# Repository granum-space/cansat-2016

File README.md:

# cansat-2016
проект команды granum конкурса cansat 2016

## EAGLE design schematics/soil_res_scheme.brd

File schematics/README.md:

# cansat-2016
Электронные схемы аппарата

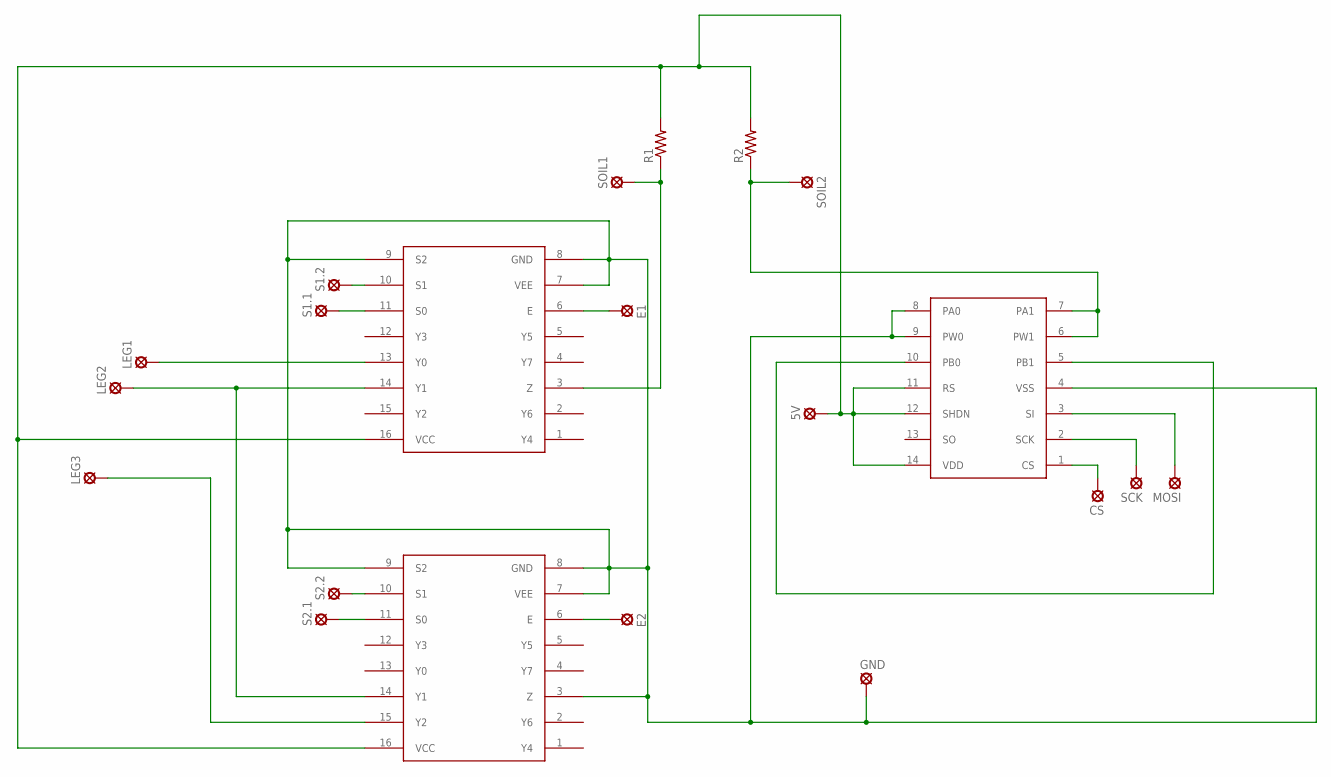
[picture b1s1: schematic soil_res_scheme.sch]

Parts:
5V: LSP10
CS: LSP10
E1, E2: LSP10
GND: LSP10
LEG1, LEG2, LEG3: LSP10
MOSI: LSP10
R1, R2: R-US_0207/10; 0207/10
S1.1, S1.2, S2.1, S2.2: LSP10
SCK: LSP10
SOIL1, SOIL2: LSP10
U$1: MCP42100!; DIL14
U$2, U$3: 74HC4051!; DIL16

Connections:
5V: 5V.MP, R1.2, R2.2, U$1.11 (RS), U$1.12 (SHDN), U$1.14 (VDD), U$2.16 (VCC), U$3.16 (VCC)
CS: CS.MP, U$1.1 (CS)
E1: E1.MP, U$2.6 (E)
E2: E2.MP, U$3.6 (E)
GND: GND.MP, U$1.4 (VSS), U$1.8 (PA0), U$1.9 (PW0), U$2.7 (VEE), U$2.8 (GND), U$2.9 (S2), U$3.3 (Z), U$3.7 (VEE), U$3.8 (GND), U$3.9 (S2)
MOSI: MOSI.MP, U$1.3 (SI)
unnamed: S2.2.MP, U$3.10 (S1)
unnamed: S2.1.MP, U$3.11 (S0)
unnamed: S1.1.MP, U$2.11 (S0)
unnamed: S1.2.MP, U$2.10 (S1)
unnamed: LEG1.MP, U$2.13 (Y0)
unnamed: LEG2.MP, U$2.14 (Y1), U$3.14 (Y1)
unnamed: LEG3.MP, U$3.15 (Y2)
unnamed: U$1.5 (PB1), U$1.10 (PB0)
SCK: SCK.MP, U$1.2 (SCK)
SOIL-1: R1.1, SOIL1.MP, U$2.3 (Z)
SOIL-2: R2.1, SOIL2.MP, U$1.6 (PW1), U$1.7 (PA1)

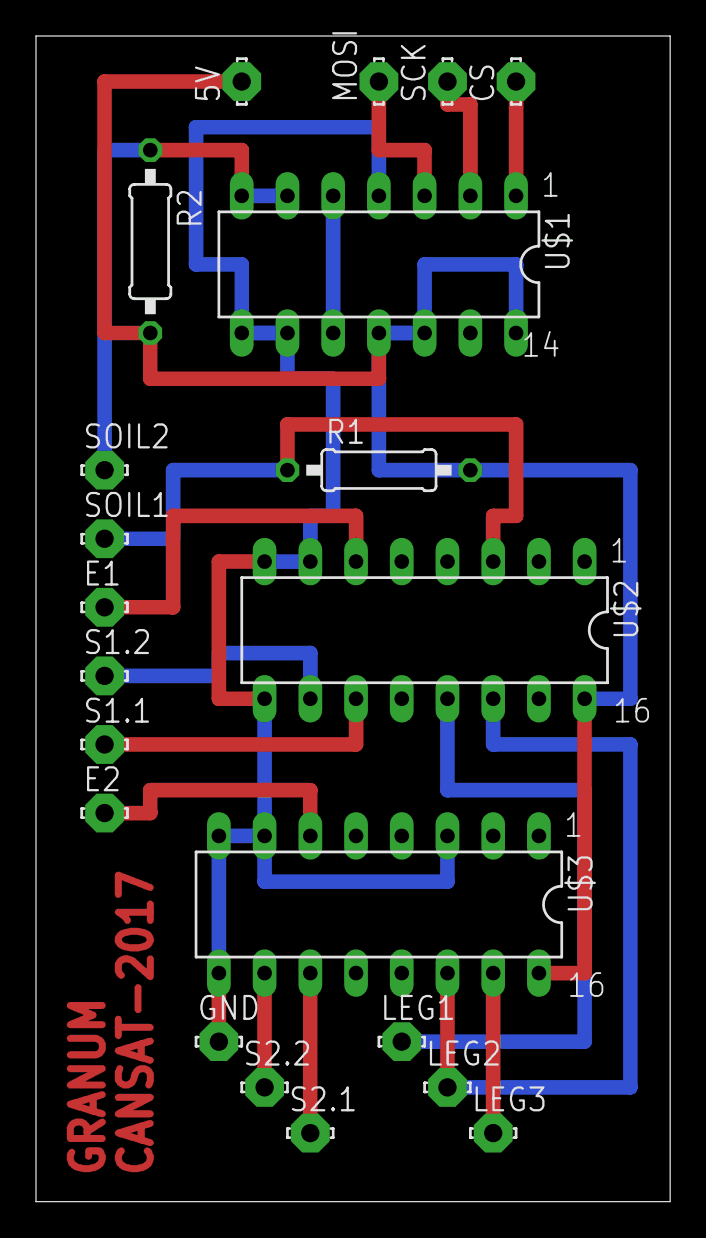
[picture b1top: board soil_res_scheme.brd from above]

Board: 2 copper layers, 35.2 x 64.8 mm, 21 parts (0 on the bottom side), 17 nets.

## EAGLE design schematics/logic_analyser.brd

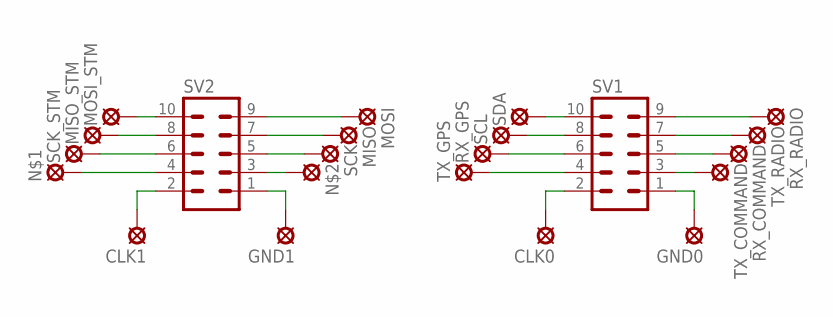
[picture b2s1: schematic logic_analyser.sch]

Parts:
CLK0, CLK1: LSP10
GND0, GND1: LSP10
MISO: LSP10
MISO_STM: LSP10
MOSI: LSP10
MOSI_STM: LSP10
N$1, N$2: LSP10
RX_COMMAND: LSP10
RX_GPS: LSP10
RX_RADIO: LSP10
SCK: LSP10
SCK_STM: LSP10
SCL: LSP10
SDA: LSP10
SV1, SV2: MA05-2
TX_COMMAND: LSP10
TX_GPS: LSP10
TX_RADIO: LSP10

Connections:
GND0: GND0.MP, SV1.1
GND1: GND1.MP, SV2.1
MISO: MISO.MP, SV2.7
MISO_STM: MISO_STM.MP, SV2.8
MOSI: MOSI.MP, SV2.9
MOSI_STM: MOSI_STM.MP, SV2.10
unnamed: N$1.MP, SV2.4
unnamed: N$2.MP, SV2.3
RX_COMMAND: RX_COMMAND.MP, SV1.5
RX_GPS: RX_GPS.MP, SV1.6
RX_RADIO: RX_RADIO.MP, SV1.9
SCK: SCK.MP, SV2.5
SCK0: CLK0.MP, SV1.2
SCK1: CLK1.MP, SV2.2
SCK_STM: SCK_STM.MP, SV2.6
SCL: SCL.MP, SV1.8
SDA: SDA.MP, SV1.10
TX_COMMAND: SV1.3, TX_COMMAND.MP
TX_GPS: SV1.4, TX_GPS.MP
TX_RADIO: SV1.7, TX_RADIO.MP

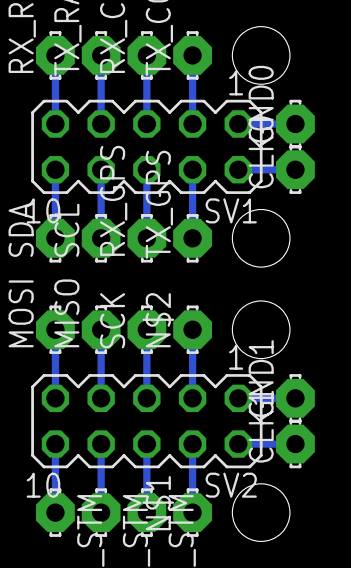
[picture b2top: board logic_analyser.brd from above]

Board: 2 copper layers, 22 parts (0 on the bottom side), 20 nets.

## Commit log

2016-10-06 Структура каталогов
2016-10-22 Принес модели корпуса
2016-11-26 Добавлена структурная схема аппарата.
2016-11-26 Поработали над документацией
    Добавили набросок для плана-графика, пояснительную записку (неполную)
    и архитектурную схему аппарата.
    Ну и обновили чертежи (на всякий случай)
2016-12-01 В пояснительную записку добавлены пункты
    5. Обоснование необходимости второго МК
    6. Эксперимент с МГМ
2016-12-03 В электрическую схему апппарата добавлены нарисованные элементы, прикреплена библиотека с ними (elements_cs2016) и еще очень много библиотек
2016-12-03 Add files via upload
    Презентация прошлого года (pdf и pptx)
2016-12-03 Заполнили план-график, добавили в ПЗ работу над ошибками, в архитектуру добавили сервомашинку
2016-12-12 Отформотированна ПЗ и обновлена прошлогодняя презентация (изменения за прошлые выходые)
2016-12-24 Подготовил описание передачи пакетов
    Осталось добавить сами пакеты, вскоре доделаю
2016-12-24 Поправил форматирование за предыдущим коммитом
2016-12-24 Добавила в презентацию таблицы с массово-габаритными параметрами и бюджетом спутника + меняю формат презентации
2016-12-24 Изменено описание протокола, обновлена архитектура.
2016-12-30 Немного подправила схему и добавила пьезо-пищалку с сервоприводом
2016-12-30 Обновляю презентацию
2016-12-30 добавляем в пояснительную записку описание измерительного моста + в схеме подключен мост, термисторы и немного по мелочам Гранум, с наступающим!
2017-01-02 Новогодний коммит! Добавила анимацию в презентацию
2017-01-03 Добвалено описание данных между STM и ATMega, добавлена схема измерительного моста.
2017-01-04 в ПЗ добавлено описание измерения твердости, в презентации изменено расширение видео, в схемах теперь подключены STM32, microSD & GPS, в библиотеке есть ATmega128
2017-01-05 Исправлена опечатка в описании способа измерения сопротивления
2017-01-05 подправила мостовую схему
2017-01-05 финальные этапы в разработке принципиальной ЭС. изменен измерительный мост, добавлены выводы для контрольно-испытательной аппаратуры, а вся аппаратура подключена к МК
    Удалены лишние файлы
2017-01-05 Подправлена архитектура (заменены дачтики)
2017-01-12 Работа над ПЗ
2017-01-14 Работа над презентацией, структурой пз, моделями
2017-01-18 Подвел ТЗ
2017-01-18 Убрал старые файлы. подработал презентацию
2017-01-19 Плоды работы за 19.01
2017-01-21 Плоды работы за 21.01
2017-01-22 заменила картинки с конструкцией в презентации и подредактировала ПЗ
2017-01-22 Финальные правки ПЗ
2017-01-22 Еще более финальные правки
2017-01-22 Исправил опечатки
2017-01-22 Еще еще более фильные правки
2017-01-22 Ну вот теперь совсем финальные правки
2017-01-22 Ну просто наифинальнейшие изменения
2017-01-22 Релиз!
2017-01-23 Доработаны модели, в презентацию добавлен слайд с рассчётом сопротивления
2017-01-26 Доработана презентация, добавлены документы с распределением ролей и текстом выступления
2017-01-27 Доработана презентация (почти окончательно), энергопотребление GPS добавлено в ПЗ, актуализарованы номера страниц в ролях и сценарии
2017-01-27 Перенес картинки в отдельную папку
2017-01-29 добавила анимацию в расширении .gif и .mp4
2017-01-30 Изменения от 29.01.17
2017-02-14 Анин корпус(немного доработан), переименовал главную сборку в all.asm
2017-03-11 готова плата с блоком переключения стержней
2017-03-14 Дал имена всем сигналам, исправил две ошибки на плате, утолщил и переразвел некоторые сигналы без переходных отверстий. (Строго говоря всеравно с ними, но они теперь в ножках микросхем)
2017-04-01 добавлена плата логического анализатора
2017-04-04 Последние версии моделек
2017-04-05 Последние версии моделей (после Вячеслава)
2017-04-07 Начато написание adxl375
2017-04-07 Начат проект под стм
2017-04-07 Работы над ADXL
2017-04-08 Изменения за 8.4.17
2017-04-11 Доработана пробка батарейного отсека
2017-04-11 потерялись
2017-04-14 Последние изменения
2017-04-15 Начат проект под STM, почти вся стандартная программа (бмп диковат) побеждена
2017-04-18 Крышка батарейного отсека с учетом крепления ключа гайков
2017-04-29 Написаны все функции, необходимые для работы с дигипотом
2017-05-02 Доведены до работы многие датчики
2017-05-02 Дигипот работает!!!
2017-05-02 Наземка доведена до очень даже рабочего состояния! (и, да, впервые закоммичена)
2017-05-03 Сделано так, чтобы работало
2017-05-03 Обновление наземки
2017-05-03 Новый rscs мастер, правильная связка с common и обновление gitignore под все конфигурации
2017-05-03 Добавил оффициальный драйвер от bosh
2017-05-03 Вариант с бошевской библиотекой для bmp280
2017-05-04 Добавил настройки
2017-05-04 Отладили
2017-05-04 Исправил настойки проекта - пересвязал с новым мастером
2017-05-06 Дописан код для дигипота для получения сопротивления с двух встроенных реостатов; Полностью дописана функция измерения (требуется тест)
2017-05-13 Повесила схему на внешний ацп, внесла изменения в функцию записи сопротивления и изменила логику измерения
2017-05-17 Самую малость поправил настройки проекта для гарантированно-корректного распознования librscs как каталога с исходными кодами
2017-05-17 it works!!1 теперь схема достаточно точно мерит сопротивление!
2017-05-19 Как давно мы не коммитили!
2017-05-19 Работа над STM частью
2017-05-20 тест схемы на предмет работы мультиплексоров
2017-05-20 в функции get_res_test() представлен иной способ нахождения минимальной разницы потенциалов
2017-05-20 На STM приём - передача SPI работает
2017-05-20 Начата интеграция GPS
2017-05-24 осуществлен более быстрый способ получения сопротивления
2017-05-24 Попытки завести GPS
2017-05-24 Накопленные изменения
2017-05-25 Распоры для резинок
2017-05-25 Передача питания через переключатель без противного кабеля
2017-05-25 Мелкие доделки, подготовка на печать
2017-05-27 Для STM32 портирован GPS-nmea модуль, настроен printf в 3 uart
2017-05-27 Обновлены структуры пакетов, добавлен кольцевой буфер для работы со значениями произвольной длины
2017-05-28 Фланец для резинок
2017-05-29 Правки фланцев под резинки и держатели для стежней на призме
2017-05-30 Призма на перепечать
2017-05-31 а вот и схемы
2017-05-31 FreeRTOS, ringbuf_varsize, исправления, причёсывание кода
2017-05-31 Комментарии к доделкам
2017-05-31 Настроил freertos, навел порядок в проекте
2017-06-01 увеличенная полость для контактного кольца
2017-06-02 Добавлена FatFS, прикручен dump
2017-06-03 Добавлены файлы модуля анализа ускорений
2017-06-03 Исправил варнинги в fatfs, пересвязался с новым мастером и подправил инклюды и конфигурации проекта
2017-06-05 Много всего для атмеги
2017-06-05 Крышка батарейного отсека переделана в надежде её таки упихать
2017-06-05 Предложения и замечания
2017-06-06 Комментарий, Правка табуляций и улучшение крышки батарейного отсека
2017-06-06 Вынес в отдельный файл опрос датчиков, добавил сохранение ошибок в пакет
2017-06-06 Держалка для стм32
2017-06-07 Правки по результатам печати
2017-06-09 Удлинитель пробки для батарейки
2017-06-12 Давно не коммитили
2017-06-15 Начата (никак не закончена!) работа по переводу всего на RTOS
2017-06-15 Замечания предложения
2017-06-15 Я, кажется, стмку почти закончил
2017-06-15 Замечания и предложения
2017-06-16 Правки, правки, исправления!
2017-06-17 Серва и пережигатели
2017-06-17 Правочки STM
2017-06-17 Указы и директивы к STM32 и несколько исправлений по ходу.
    Скорее всего это нужно вмержить в мастер, тут много чего настроено в плане конфигураций.
2017-06-17 ВОЙНА ВАРНИНГАМ
    И теперь проект хотябы компилится моим компилятором. По остальным старым замечаниям по прежнему нет реакции
2017-06-22 Стоит коммитить чаще.
2017-06-24 Почти доделана атмега, исправлено много ошибок и замечаний на стм
2017-06-27 Пляски над стмкой
2017-06-28 5 дней до краха
2017-06-29 Колдунства Василия над СТМ
2017-06-29 Исправлены частоты SPI и откалибрована серва 4 дня до краха
2017-06-29 Починил GPS?
2017-06-29 Чистка мусора
2017-06-29 Вроде ничего не забыл - теоретически все работает
2017-06-29 Теперь атмега компилится
2017-06-29 Забытое
2017-06-30 Исправил ошибку с кареткой DMA в gps модуле. Вынес инициализационные структуры в отдельные "scope", чтобы уменьшить требования к стеку
2017-06-30 Кажется теперь все работает!
2017-07-01 Что-то работает
2017-07-02 Немного приблизились к полной работоспособности
2017-07-02 Доделки наземки
2017-07-02 Sync
2017-07-02 GPS Теперь фильтрует плохие сообщения. Вроде
2017-07-02 ПРавки для отладки блокировки по ускорениям
2017-08-08 Финальный коммит (с опозданием на месяц. И да, мы летели не спуллив последние 4 коммита из гита. Косяк! Косяк!) Всем спасибо за это "Творчество".
2017-09-26 Презентация
    Не последняя версия, но другой у меня нет
2017-11-28 Презентация с летней сессии
2018-07-21 бэкпорт фикса страшнючего бага
